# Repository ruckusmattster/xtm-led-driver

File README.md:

<div align="center">

# XTM LED Driver

**A flicker-free, four-decade DC LED driver for theatrical fixtures.**<br>
1.4 A down to 5 µA as pure DC: no PWM anywhere, nothing for a camera to catch.

[**Build guide**](docs/BUILD_GUIDE.md) ·
[**Design process**](docs/DESIGN_PROCESS.md) ·
[Hardware](docs/HARDWARE.md) ·
[Firmware](docs/FIRMWARE.md) ·
[Design record](docs/design-record/)

</div>

---

I'm building four stage fixtures around the **Xicato XTM19803050CCA** (19 mm LES, 3000 K, about
5000 lm at 1.4 A). Off-the-shelf drivers either dim with PWM, which rolling-shutter cameras turn
into bands, or bottom out around 1%, which makes the end of every fade snap to black. This
project is a two-board driver that does neither: the LED current is DC at every level from full
output down to 5 µA (0.0004%), fades are smooth enough to film in 240 fps slow motion, and each
fixture is a normal dimmable light in Home Assistant with a knob on the back and a sync button
that makes the others follow it.

Everything is here: the schematics (as code), the design calculations and simulations, scripted
KiCad 9 layouts that come out DRC-clean, Gerbers and placement files, BOMs with verified part
numbers, firmware for both boards with its tests, and the procedures to bring it up, calibrate
it and prove it doesn't flicker.

## Highlights

- **Four DC ranges, not PWM.** Four linear current sinks with 0.1 Ω, 1 Ω, 10 Ω and 100 Ω shunts
  sit in parallel under the LED. Each covers a decade at the same 14–140 mV sense voltage, so
  every range is equally precise, and a calibrated tail carries the last decade and a half to 5 µA.
- **Crossovers you can't see.** Where two ranges meet, both channels share the current on a
  log-domain blend, and the incoming channel idles at a small keep-alive current so it's already
  regulating when it's needed. Simulated deviation at a crossover: 0.14% on a 10 s fade.
- **A tracking buck that stays out of the picture.** A forced-PWM buck at 400 kHz holds the LED
  anode about 1 V above what the sinks need, set ahead of every current change by the MCU. Its
  ripple sits far above anything a camera or eye integrates.
- **Precision where it counts.** 16-bit DAC, zero-drift op-amps, Kelvin-sensed shunts (a
  four-terminal 0.1 Ω and 0.1% thin film for the rest), a guarded "precision island" on a 4-layer board. After calibration each range
  holds about ±0.1% of reading.
- **Real-time control on the driver.** An STM32G431 runs fades at 4 kHz, the crossovers, the
  headroom loop and the protection (a shorted LED clamps every sink within 100 µs). Wi-Fi never
  touches the light.
- **A friendly controller.** Board B is a socketed Waveshare ESP32-S3-Zero running ESPHome:
  Home Assistant light, rotary encoder with push, status LED, and fixture-to-fixture sync over
  ESP-NOW with authenticated packets. Every fixture also works completely on its own.
- **Layout by script.** Python scripts place every part, draw the critical copper by hand-coded
  rules, route the rest with Freerouting, pour and stitch ground, run DRC and export JLCPCB files.
  Both boards come out with 0 errors and 0 unconnected items.

## How it works

```mermaid
flowchart TB
  mains(["Mains"]) --> psu["Mean Well LRS-100-48<br/>isolated 48 V, off-board"]
  subgraph A["Board A · driver · 90 × 60 mm, 4 layers"]
    fuse["Fuse + TVS"] --> buck["Tracking buck<br/>LMR38020, forced PWM"]
    fuse --> aux["Aux buck + LDOs<br/>5.5 V · 5 V · 3.3 V"]
    mcu["STM32G431<br/>4 kHz control loop"] -->|SPI| dac["DAC80504<br/>4 × 16-bit"]
    dac --> sinks["OPA4388 + 4 linear sinks<br/>0.1 Ω · 1 Ω · 10 Ω · 100 Ω"]
    mcu -->|"DAC → feedback"| buck
    sinks -.->|"cathode tap<br/>fast trip"| mcu
  end
  subgraph L["LED"]
    led(["Xicato XTM<br/>up to 1.4 A"])
  end
  subgraph B["Board B · controller · 60 × 45 mm"]
    knob["Encoder · push · sync"] --> esp["ESP32-S3-Zero<br/>ESPHome"]
  end
  ha(["Home Assistant"])
  other(["Other fixtures"])
  psu -->|"48 V DC"| fuse
  buck -->|"LED+"| led
  led -->|"LED−"| sinks
  mcu ---|"10-way ribbon<br/>UART · 5.5 V · reset"| esp
  esp -.-|"Wi-Fi"| ha
  esp -.-|"ESP-NOW"| other
```

The **sinks** set the LED current; the **buck** only supplies the voltage they need. Board A's
MCU knows the LED's forward voltage at every current (it learns it as it runs), so on a rising
cue it raises the buck first and then the current, and on a falling cue the reverse. Only a
level, a fade time and status cross the ribbon to Board B.

<picture>
  <source media="(prefers-color-scheme: dark)" srcset="docs/images/ranges-dark.png">
  
</picture>

Brightness is exponential in the setting, so every step looks the same size: 1% of the scale is
about 13% more light, from 5 µA at the bottom to 1.4 A at the top.

<picture>
  <source media="(prefers-color-scheme: dark)" srcset="docs/images/curve-dark.png">
  
</picture>

## The boards

| | Board A: driver | Board B: controller |
| --- | --- | --- |
| **Top** |  |  |
| **Bottom** |  |  |
| Size | 90 × 60 mm, 4 layers, ENIG | 60 × 45 mm, 2 layers, ENIG |
| Parts | 206 on 96 nets | 42 on 32 nets |
| Does | 48 V in, tracking buck, four sinks, protection, fades, calibration | Wi-Fi and Home Assistant, knob, sync, status LED |
| Key parts | STM32G431CBU6, DAC80504, OPA4388, 2 × LMR38020, NDT3055L, WSK2512 | Waveshare ESP32-S3-Zero-M on sockets, Bourns PEC11R encoder |
| Layout result | 0 DRC errors, 0 unconnected | 0 DRC errors, 0 unconnected |

Renders are bare boards from KiCad (no 3D models for the parts). The ESP32-S3-Zero plugs into
two sockets on Board B's back, so it can be pulled out and flashed over its own USB-C.

## Specifications

Design values from the calculations and simulations in [`design/`](design/). None of this has
been measured on hardware yet.

| Parameter | Design value |
| --- | --- |
| Output | 5 µA to 1.4 A DC (1.5 A with tolerance), four ranges plus a calibrated tail |
| Brightness curve | Exponential: 0–100% → 5 µA–1.4 A, about 13% more light per 1% step |
| Flicker target | Under 1% at any frequency from 100 Hz to 20 kHz, at every level and during fades |
| Accuracy after calibration | ±0.09–0.11% RSS in each range; ±0.6% at 14 µA and ±1.6% at 5 µA |
| Crossover smoothness | 0.11–0.14% on a 10 s full-range fade, 0.9–1.5% on a 1 s fade (simulated) |
| Response | Snaps within 5 ms; fades updated at 4 kHz, from instant to 10 minutes |
| Input | 48 V DC (43.2–52.8 V) from a Mean Well LRS-100-48; about 45 W at full output |
| LED voltage | 3.5 V floor to 38 V usable, 40.4 V hard ceiling |
| Protection | Shorted LED (every sink clamped within 50–100 µs), open LED, undervoltage, four temperature sensors with derating, DAC read-back, watchdog, 3 A fuse, TVS on input and output |
| Link loss | Board A blinks twice and settles at 20% if Board B goes quiet; planned restarts hold the level |
| Control | Home Assistant (ESPHome native API), encoder with push, sync button and a header for a panel-mount button |
| Group sync | ESP-NOW broadcast, fixture to fixture, HMAC-SHA256 authenticated; no router or HA in the path |

## Status

| Stage | State |
| --- | --- |
| ✅ Circuit design, calculations, crossover simulation | Done; `design/calc.py` asserts the limits that matter |
| ✅ Schematics (as code) with connectivity check | Done; 0 ERC errors on both boards |
| ✅ Part numbers | Every numbered part checked against a distributor or manufacturer page (29 Sep 2026) |
| ✅ PCB layout | Done by script; both boards 0 DRC errors, 0 unconnected |
| ✅ Board A firmware | Builds (50–58 KB of 126 KB, depending on the toolchain); 97,146 host-test checks pass |
| ✅ Board B firmware | ESPHome config validates; 89 unit checks and a 43-check end-to-end test on ESPHome's Linux build pass |
| ⏳ ESP32-S3 build | Not yet run; the CI workflow in `.github/workflows/` runs it on every push |
| ⏳ Fabrication, assembly, bring-up, flicker measurements | Not started |
| ⚠️ Known firmware issue | Board A detects an open LED only near full output, and learns a bad correction while the LED is disconnected; see [known issues](docs/FIRMWARE.md#known-issues) |

If you build one before I do, I'd love to hear how it went.

## Repository map

```text
xtm-led-driver/
├── design/                 schematics as code, calculations, simulation
│   ├── board_a.py          every Board A part and pin-to-net connection
│   ├── board_b.py          the same for Board B
│   ├── catalog.py          part data: MPNs, LCSC numbers, footprints, verification notes
│   ├── build.py            regenerates hardware/ and runs the connectivity check (ERC)
│   ├── calc.py             every design number; prints calc_output.txt
│   ├── sim/handover.c      time-domain model of a crossover between two sinks
│   ├── compare_netlists.py checks your own KiCad schematic against the generated netlist
│   └── kicad_pos_to_jlc_cpl.py   KiCad position file → JLCPCB CPL, with rotation fixes
├── hardware/               generated from design/: per board, sheet tables, netlist, BOMs
│   ├── board_a/  board_b/
│   ├── board_a.kicad_dru   custom DRC rules (48 V spacing, precision-island clearance)
│   └── LAYOUT.md           the layout rules the scripts follow and you review against
├── layout/                 scripted KiCad 9 layout + Freerouting
│   ├── run_layout.bat      Windows launcher (double-click)
│   ├── make_board.py       stages: place, route, pour, stitch, DRC, export
│   ├── board_a_layout.py   Board A placement, hand-drawn copper, pours, rules
│   ├── board_b_layout.py   Board B the same
│   ├── lib/XTM.pretty/     this project's ESP32-S3-Zero socket footprint
│   └── out/                the finished boards: KiCad projects, Gerbers, CPL, DRC reports
├── firmware/
│   ├── board-a/            STM32G431 firmware in C (CMake), host tests, calibrate.py, flicker.py
│   └── board-b/            ESPHome configs + the xtm_driver external component, tests
└── docs/
    ├── BUILD_GUIDE.md      how to use these files and build the whole thing
    ├── DESIGN_PROCESS.md   how the design got here, and why
    ├── HARDWARE.md         circuit reference
    ├── FIRMWARE.md         firmware reference
    └── design-record/      the Phase 1 review and Phase 2 detailed design, as written
```

## Quick start

**Just want the boards?** The finished layouts are in [`layout/out/`](layout/out/): upload
`board_a-gerbers.zip` and `board_b-gerbers.zip` to JLCPCB with the settings in
[the build guide](docs/BUILD_GUIDE.md#6-order-the-pcbs-and-stencils), and order parts from the
hand-assembly BOMs in [`hardware/`](hardware/). Read [section 5](docs/BUILD_GUIDE.md#5-review-before-ordering)
first.

**Want to check or change the design?**

```sh
python3 design/build.py            # regenerate netlists and BOMs, run the connectivity check
python3 design/calc.py             # every design number (needs numpy, and gcc for the simulation)
make -C firmware/board-a/tests     # Board A host tests
make -C firmware/board-b/tests     # Board B unit tests
layout\run_layout.bat              # both layouts, on Windows with KiCad 9 and Java 21
```

**Building the firmware?**

```sh
cd firmware/board-a
cmake -B build -G Ninja -DCMAKE_TOOLCHAIN_FILE=cmake/arm-none-eabi.cmake && cmake --build build

cd ../board-b
cp secrets.yaml.example secrets.yaml   # fill in Wi-Fi and keys
esphome run xtm-1.yaml
```

The [build guide](docs/BUILD_GUIDE.md) walks through all of it, from installing the tools to a
calibrated, flicker-tested fixture.

## Documentation

| Document | What's in it |
| --- | --- |
| [Build guide](docs/BUILD_GUIDE.md) | Every step to make one yourself: tools, files, ordering, assembly, flashing, bring-up, calibration, flicker testing, use, troubleshooting, pinouts |
| [Design process](docs/DESIGN_PROCESS.md) | From a 0–10 V dimmer idea to this: the requirements, the reviews, the decisions and what changed them |
| [Hardware reference](docs/HARDWARE.md) | Both boards block by block, with values and the reasoning behind them |
| [Firmware reference](docs/FIRMWARE.md) | Board A's control loop, the link protocol, the ESPHome component |
| [Layout scripts](layout/README.md) | Running and changing the automated layout |
| [Layout rules](hardware/LAYOUT.md) | Stackup, floorplan, power and sense routing, clearances |
| [Design record](docs/design-record/) | The Phase 1 review and the Phase 2 detailed design, complete, as written |

## The design in one chart

The first plan used PWM for the bottom decade and handed the current between ranges with a
simple crossfade. Working through the dynamics showed the crossfade would dip the light by up to
17% on a fast fade, because the incoming channel starts from a wound-down integrator. Priming it
with a keep-alive current and blending in the log domain fixed it:

<picture>
  <source media="(prefers-color-scheme: dark)" srcset="docs/images/crossover-dark.png">
  
</picture>

That story, and the others like it, are in [the design process](docs/DESIGN_PROCESS.md).

## Safety

Board A runs from 48 V and can put 38 V on the LED connector. Neither board carries mains: the
48 V comes from a separate, certified, isolated supply (Mean Well LRS-100-48) with its own fused
inlet. Wire and enclose the mains side of that supply properly, or have someone qualified do it.
Never plug or unplug the LED while the output is on.

## Acknowledgements

- [KiCad](https://www.kicad.org), [Freerouting](https://github.com/freerouting/freerouting),
  [ESPHome](https://esphome.io) and [Home Assistant](https://www.home-assistant.io) do the heavy
  lifting.
- `firmware/board-a/third_party/` carries Arm's CMSIS (Apache-2.0) and ST's STM32G4 device files
  (Apache-2.0) and LL drivers (BSD-3-Clause), under their own licences.
- The ESP32-S3-Zero footprint's pin order was cross-checked against
  [jtomka/kicad-esp32-s3-zero](https://github.com/jtomka/kicad-esp32-s3-zero).

## License

Not chosen yet. Until a `LICENSE` file is added, the default applies: all rights reserved,
except the third-party files under their own licences.

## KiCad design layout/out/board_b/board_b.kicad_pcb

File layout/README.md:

# Board layout scripts

These scripts turn the two netlists in `design/` into finished KiCad 9 boards and JLCPCB files,
without anyone drawing the layout by hand. For each board they:

1. build the outline, mounting holes, slots and keep-outs, and place every part: the connectors,
   ICs and power parts at fixed coordinates, the small parts next to the pins they serve;
2. draw the copper that decides whether the board works before anything is routed: both switch
   nodes and bootstrap links (L1 only, no vias), the fused 48 V input and the +48V trunk to the
   buck, Q1's source to its shunt, the ch2 shunt ladder's bus bars, the CATHODE tab copper and heat
   spreader with its vias, the L2 ground plane, escapes for the few pins the router can't get out
   of, and a via to the plane beside every ground pad, while there's still room for them;
3. route everything else with Freerouting (kept out of the CATHODE copper), clean up what it
   leaves (stubs, doubled segments, dangling vias), and route again whatever is still open;
4. pour ground, stitch every pour fragment and pad the pours miss, place the reference labels;
5. run KiCad's DRC with the project's custom rules (`hardware/board_x.kicad_dru`: the 48 V
   spacing from IPC-2221B, 0.5 mm where a bare pad is involved and 0.3 mm between coated tracks;
   2 mm between precision and HV nets; 10 mm from the switch nodes; no vias on them);
6. export Gerbers, drill files and a JLCPCB placement file, and preview images.

The result is a normal KiCad project you open, inspect and adjust like one you drew yourself.

## What you need

- **KiCad 9.0** (any 9.0.x) from https://www.kicad.org/download/windows/ , installed to its default
  folder. Nothing else from KiCad: the scripts use its own Python and `kicad-cli`.
- **A Java 21 runtime** for Freerouting. From a Command Prompt:
  `winget install EclipseAdoptium.Temurin.21.JRE` (or the Temurin 21 JRE installer from
  https://adoptium.net with "Add to PATH" ticked). Open a new Command Prompt afterwards.
- **Internet on the first run**, to download Freerouting 1.9.0 (5 MB, from its GitHub releases)
  into `layout\tools\`. If that's blocked, download `freerouting-1.9.0.jar` from
  https://github.com/freerouting/freerouting/releases/tag/v1.9.0 into `layout\tools\` yourself, or
  set `FREEROUTING_JAR` to where you put it. (Board B's footprint for the ESP32-S3-Zero on its
  sockets is this project's own, in `lib\XTM.pretty`.)

Freerouting 1.9.0 rather than the newer 2.x on purpose: on Board A, 2.1 left over a hundred
connections open where 1.9 leaves a handful, and 2.1 ignores its pass limit.

## Running it

Double-click `run_layout.bat`, or from a Command Prompt in this folder:

```bat
run_layout.bat                          :: both boards, start to finish
run_layout.bat board_b                  :: one board
run_layout.bat board_a --stage place    :: placement only, with a preview (a minute)
run_layout.bat board_a --attempts 10    :: more routing attempts (each board tries 6 by default)
```

Board B takes a few minutes and Board A 5 to 30, most of it in Freerouting, which opens its own
window while it works and closes it when it's done: leave it alone. The same command in the
"KiCad 9.0 Command Prompt" (Start menu) is `python make_board.py board_a`.

Each run writes `out\board_a\` (or `board_b`):

| File | What it is |
| --- | --- |
| `board_a.kicad_pro`, `.kicad_pcb`, `.kicad_dru` | The KiCad project: open the `.kicad_pro` |
| `board_a-gerbers.zip` | Gerbers and drill files for JLCPCB, ready to upload |
| `board_a-cpl-jlc.csv` | Placement file in JLCPCB's format (`board_a-pos.csv` is KiCad's own) |
| `board_a_drc.json` | The final DRC report |
| `board_a-1-FCu_FSilkS.png` and the others | Preview images of each copper layer (SVG if no PNG converter) |
| `board_a_run.log` | What happened, with the DRC summary at the end |
| `board_a_freerouting-1.log`, `.dsn`, `.ses` | The router's input, output and log |

The last line of the log reads `done in ... s: 0 DRC errors, 0 unconnected` when the board is
complete. `run_layout.bat` says so too, and exits with an error otherwise.

## If connections are left open

Freerouting's result changes from run to run. If the log ends with a few connections open:

1. Run the board again, perhaps with `--attempts 10`; each attempt clears a wider circle
   around what's still open before routing it again; or
2. open `out\board_a\board_a.kicad_pro` in KiCad, route the ratsnest lines that remain (they're
   listed in the log), press **B** to refill the zones, save, close KiCad, and run
   `run_layout.bat board_a --stage export`. That re-stitches the pours, re-runs the DRC and writes
   new Gerbers and placement files without touching anything you drew.

The export stage is also how to regenerate the outputs after any hand edit. Running the full
script again starts over from the netlist and discards hand edits.

## Checking the result before ordering

Open each `.kicad_pro` in KiCad 9 and go through this list. The DRC covers the numeric rules; these
are the things a rule can't see.

- **Inspect > Design Rules Checker**, "Refill all zones" ticked: no errors, nothing unconnected.
  Silkscreen warnings are fine; look at any that sit on a pad.
- **View > 3D Viewer**: every part present and on the right side; J1, J2 and J3's openings face
  off the board. Board B's U1 is on the back, shown by its outline on the F.Fab/B.Fab layers
  (there's no 3D model for the module).
- Board A power stage: U2's SW pin, C23 and L2 pad 1 joined by short, wide copper on L1 with no
  vias (the same for U3, C3 and L3); C22 right at U2's VIN pin with a ground via beside it.
- Board A cathode: J2 pin 1, C60, R110 and the four drains all on the tab copper; the heat
  spreader under it on the bottom layer, joined by the grid of vias; R102 at least 2 mm from it.
- Board A sinks: each channel's SNSHI and SNSLO tracks start at the shunt's Kelvin pads (R102
  pads 2 and 3; NT1/NT2 at the ladder's mid-points; NT3–NT6 at R100 and R101); the divider
  bottoms (R46, R48, R50, R52) and C44–C47 return to SNSLO, not to ground.
- Board A precision island: nothing from the switch nodes nearby; the DRC's 2 mm rule keeps HV
  copper away.
- Board B: U1's two socket rows on the back, pin 1 (square pad) at the USB-C end nearest the
  middle of the board; no copper on either side under the antenna end at the right-hand edge.
  Print the board 1:1 (File > Plot, B.Cu, B.SilkS and Edge.Cuts to PDF, mirrored) and lay the
  module on it, pins into the pads, before ordering.
- Holes: Board A's four M3 holes and Board B's two are unplated, with nothing inside their rings.
- The Gerbers in KiCad's Gerber viewer (or JLCPCB's): four copper layers for Board A and two for
  Board B, the slot between J2's pads in the drill/outline file, paste layers present.

References that didn't fit on the silkscreen are on the F.Fab layer: for hand assembly, print it
(File > Plot, F.Fab and Edge.Cuts to PDF) as the assembly drawing.

At JLCPCB: upload the Gerber zip; for assembly, use `hardware/board_x/board_x-bom-jlc.csv` as the
BOM and `board_x-cpl-jlc.csv` as the placement file, and check every part's rotation in their
preview (their library's zero angle doesn't always match KiCad's; polarised parts and the ICs are
the ones to look at).

## What the scripts don't do

- They don't keep each Kelvin pair (SNSHIx with SNSLOx) side by side: the router draws them
  separately. They start at the right sense points, which is what matters most at these slow
  signals; redrawing them as pairs by hand is the one refinement worth the time.
- The router doesn't know which tracks matter more than others: look over the power stage, the
  sinks and the precision island against `hardware/LAYOUT.md` before ordering.
- Freerouting's result varies from run to run, and the placement of small parts follows simple
  rules; a second run can come out better or worse.

## Changing the layout

Everything that decides the layout is in `board_a_layout.py` and `board_b_layout.py`:

- `L.place("U2", 53.1, 40.5, 270)`: fixed parts, in mm from the board's top-left corner, rotation
  in degrees counter-clockwise. Move one, run `--stage place` to see it, then run the whole board.
- `A([...], Rect(x0, y0, x1, y1), anchor_pad=...)`: small parts placed automatically inside the
  rectangle, as close as possible to the pad named (decoupling capacitors) or to the parts they
  connect to. `SPACING` sets the room left between them for routing.
- `NET_CLASSES` and `PATTERNS`: track widths and clearances per net. The widths have to fit the
  pins a net lands on (0.2 mm reaches the 0.5 mm-pitch QFN pins).
- `prerouted()`, `cathode_copper()` and `finish()`: the copper drawn by hand and the pours.
- `SPEC`: how the board is routed: attempts and the time each may take, whether to start over
  every few attempts (`restart_every`, Board B) or keep repairing (Board A), the ground fan-out,
  and which nets are poured rather than routed.

The netlists themselves come from `design/board_a.py` and `design/board_b.py`; after changing
those, run `python design/build.py` (BOMs, sheet tables and netlists) and then the layout.

## Files

| File | Role |
| --- | --- |
| `make_board.py` | The run itself: stages, routing attempts, checks, outputs |
| `board_a_layout.py`, `board_b_layout.py` | Each board's placement, pre-drawn copper, pours and rules |
| `pcbkit.py` | Building a board from a netlist: footprints, placement, tracks, vias, zones, keep-outs |
| `route.py` | Freerouting round trip, clean-up, stitching, DRC, previews, fabrication outputs |
| `kicadlib.py` | Finds KiCad 9's footprint libraries, and this project's own in `lib\` |
| `run_layout.bat` | Windows launcher: finds KiCad and Java, runs both boards |

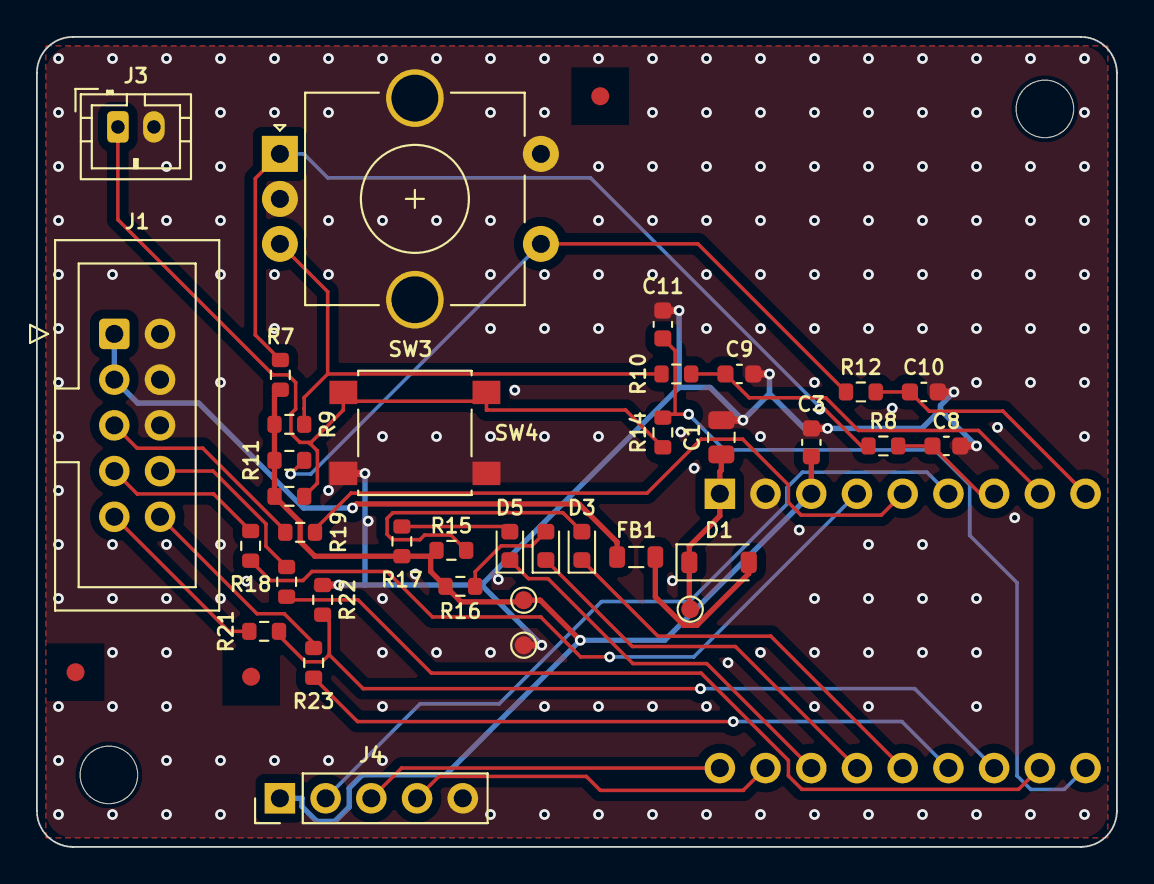
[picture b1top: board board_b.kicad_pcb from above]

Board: 2 copper layers, 60.0 x 45.0 mm, 42 parts (1 on the bottom side), 32 nets.

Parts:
C1: 10uF; C_0805_2012Metric
C3: 100nF; C_0603_1608Metric
C8, C9, C10, C11: 10nF; C_0603_1608Metric
D1: B5819W; D_SOD-123
D3: red; LED_0603_1608Metric
D4: green; LED_0603_1608Metric
D5: blue; LED_0603_1608Metric
FB1: 600R@100MHz 2A; L_0805_2012Metric
FID1, FID2, FID3: FID; Fiducial_1mm_Mask2mm
H1, H2: M3; MountingHole_3.2mm_M3
J1: 2x5 box header; IDC-Header_2x05_P2.54mm_Vertical
J3: JST PH 2; JST_PH_B2B-PH-K_1x02_P2.00mm_Vertical
J4: 1x5 header; PinHeader_1x05_P2.54mm_Vertical
R7, R8, R9, R10, R11, R12, R13, R14: 10k; R_0603_1608Metric
R15: 1k; R_0603_1608Metric
R16, R17: 220R; R_0603_1608Metric
R18, R19, R20, R21, R23: 100R; R_0603_1608Metric
R22: 100k; R_0603_1608Metric
SW3: PEC11R-4220F-S0024; RotaryEncoder_Alps_EC11E-Switch_Vertical_H20mm_CircularMoun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
SW4: SYNC; SW_SPST_B3S-1000
TP1, TP2, TP3: TP; TestPoint_Pad_D1.0mm
U1: ESP32-S3-Zero-M; ESP32-S3-Zero_Socket

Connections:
+3V3: C3.1, J4.1, R7.1, R9.1, R11.1, R13.1, R15.1, R16.1, R17.1, TP2.1, U1.3
+5V5_F: D1.2, FB1.2
+5V5_IN: FB1.1, J1.1, J1.3
+5V_SYS: C1.1, D1.1, TP1.1, U1.1
A_OK: J1.9, R21.1
A_OK_IN: R21.2, R22.1, U1.12
BOOT0_A: J1.8, R20.2
BOOT0_OUT: R20.1, U1.11
ENC_A: C8.1, R8.2, U1.7
ENC_A_RAW: R7.2, R8.1, SW3.A
ENC_B: C9.1, R10.2, U1.8
ENC_B_RAW: R9.2, R10.1, SW3.B
ENC_SW: C10.1, R12.2, U1.9
ENC_SW_RAW: R11.2, R12.1, SW3.S1
GND: C1.2, C3.2, C8.2, C9.2, C10.2, C11.2, J1.2, J1.4, J1.6, J3.2, J4.5, R22.2, SW3.C, SW3.MP, SW3.S2, SW4.2, TP3.1, U1.2
LED_B: D5.1, U1.16
LED_B_A: D5.2, R17.2
LED_G: D4.1, U1.15
LED_G_A: D4.2, R16.2
LED_R: D3.1, U1.14
LED_R_A: D3.2, R15.2
LINK_RX: R19.2, U1.5
LINK_TX: R18.1, U1.4
NRST_A: J1.10, R23.2
NRST_OUT: R23.1, U1.13
RXD_A: J1.7, R18.2
SPARE_IO3: J4.2, U1.6
SPARE_IO43: J4.3, U1.18
SPARE_IO44: J4.4, U1.17
SYNC: C11.1, R14.2, U1.10
SYNC_RAW: J3.1, R13.2, R14.1, SW4.1
TXD_A: J1.5, R19.1

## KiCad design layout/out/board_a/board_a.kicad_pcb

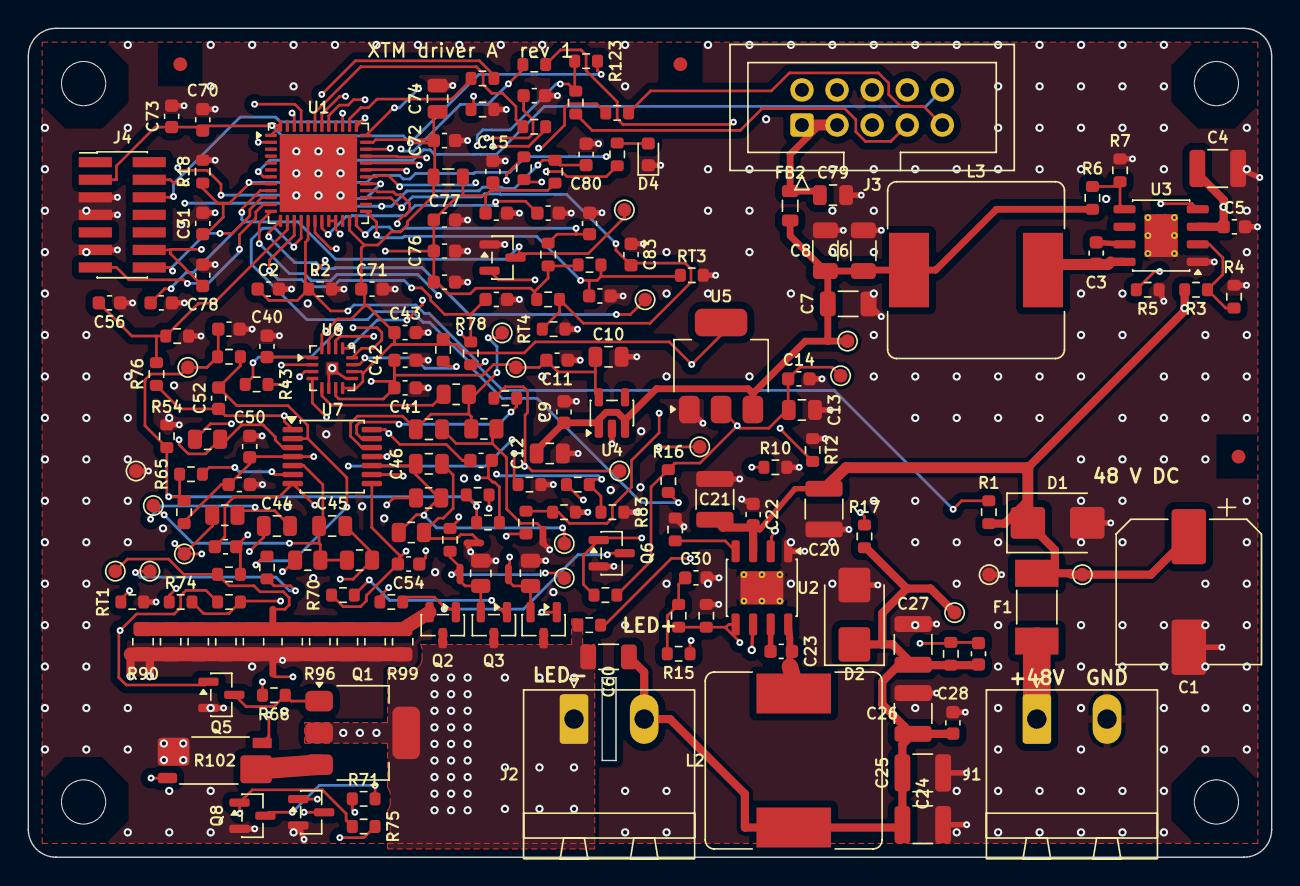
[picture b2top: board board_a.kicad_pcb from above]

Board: 4 copper layers, 90.0 x 60.0 mm, 206 parts (0 on the bottom side), 96 nets.

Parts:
C1: 47uF 100V; CP_Elec_10x10
C2, C31, C80, C81, C82, C83: 10nF; C_0603_1608Metric
C3, C11, C14, C16, C23, C41, C43, C50, C70, C71, C72, C73, C76, C77, C78: 100nF; C_0603_1608Metric
C4, C20, C21, C24, C25, C26, C27: 4.7uF 100V; C_1210_3225Metric
C5, C22, C28: 100nF 100V; C_0603_1608Metric
C6, C7, C8: 22uF; C_1206_3216Metric
C9, C15, C42, C48, C51, C75: 1uF; C_0603_1608Metric
C10, C12, C74: 4.7uF; C_0805_2012Metric
C13, C79: 10uF; C_0805_2012Metric
C29: 22pF C0G; C_0603_1608Metric
C30: 47nF; C_0603_1608Metric
C40: 220nF; C_0603_1608Metric
C44, C45, C46, C47: 10nF C0G; C_0805_2012Metric
C52, C53, C54, C55: 2.2nF C0G; C_0603_1608Metric
C56, C57, C58, C59, C61: 1nF C0G; C_0603_1608Metric
C60: 22nF 100V; C_1206_3216Metric
D1: SMBJ58A; D_SMB
D2: SMBJ43A; D_SMB
D3: BAV199; SOT-23
D4: green; LED_0603_1608Metric
F1: 3A T; Fuse_Littelfuse-NANO2-451_453
FB1: 600R@100MHz; L_0805_2012Metric
FB2: 600R@100MHz 2A; L_0805_2012Metric
FID1, FID2, FID3: FID; Fiducial_1mm_Mask2mm
H1, H2, H3, H4: M3; MountingHole_3.2mm_M3
J1, J2: MSTBA 2,5/2-G-5,08; PhoenixContact_MSTBA_2,5_2-G-5,08_1x02_P5.08mm_Horizontal
J3: 2x5 box header; IDC-Header_2x05_P2.54mm_Vertical
J4: STDC14; PinHeader_2x07_P1.27mm_Vertical_SMD
L2: 33uH; L_Bourns_SRR1260
L3: 15uH; L_Bourns_SRR1260
NT1, NT2, NT3, NT4, NT5, NT6: NetTie; NetTie-2_SMD_Pad0.5mm
Q1: NDT3055L; SOT-223-3_TabPin2
Q2, Q5, Q6, Q7, Q8: 2N7002BK; SOT-23
Q3, Q4: 2N7002; SOT-23
R1, R6, R10, R16, R72, R73, R74, R75, R76, R77, R78, R79, R80, R81, R82, R83, R123: 100k; R_0603_1608Metric
R2: 6.2k; R_0603_1608Metric
R3: 280k; R_0603_1608Metric
R4, R44, R53, R120, R126, R127, R128, R129: 10k; R_0603_1608Metric
R5: 52.3k; R_0603_1608Metric
R7: 22.1k; R_0603_1608Metric
R11: 64.9k; R_0603_1608Metric
R12: 200k; R_0603_1608Metric
R13: 7.32k; R_0603_1608Metric
R14, R15: 8.25k; R_0603_1608Metric
R17, R110: 1M; R_0603_1608Metric
R18: 82k; R_0603_1608Metric
R40, R41, R42, R43: 22R; R_0603_1608Metric
R45, R47, R49, R51: 12.0k 0.1%; R_0805_2012Metric
R46, R48, R50, R52: 1.00k 0.1%; R_0805_2012Metric
R54, R60, R61, R62, R63, R125: 1k; R_0603_1608Metric
R64, R65, R66, R67: 1.82M; R_0603_1608Metric
R68, R69, R70, R71: 220R; R_0603_1608Metric
R90, R91, R92, R93, R94, R95, R96, R97, R98, R99, R100: 10R 0.1%; R_0805_2012Metric
R101: 100R 0.1%; R_0805_2012Metric
R102: 0.1R 4T; R_Shunt_Vishay_WSK2512_6332Metric_T1.19mm
R121, R122, R124: 100R; R_0603_1608Metric
RT1, RT2, RT3, RT4: 10k NTC; R_0603_1608Metric
TP1, TP2, TP3, TP4, TP5, TP6, TP7, TP8, TP9, TP10, TP11, TP12, TP13, TP14, TP15, TP16, TP17, TP18, TP19: TP; TestPoint_Pad_D1.0mm
U1: STM32G431CBU6; QFN-48-1EP_7x7mm_P0.5mm_EP5.6x5.6mm
U2, U3: LMR38020FDDAR; HSOP-8-1EP_3.9x4.9mm_P1.27mm_EP2.41x3.1mm_ThermalVias
U4: TPS7A2050PDBVR; SOT-23-5
U5: LDL1117S33R; SOT-223-3_TabPin2
U6: DAC80504RTET; Texas_RTE0016D_WQFN-16-1EP_3x3mm_P0.5mm_EP0.8x0.8mm
U7: OPA4388IPWR; TSSOP-14_4.4x5mm_P0.65mm

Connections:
+3V3: C13.1, C14.1, C43.1, C70.1, C71.1, C72.1, C73.1, C74.1, D3.2, FB1.1, J4.3, R16.2, R44.2, R72.2, R73.2, R74.2, R75.2, R123.2, TP4.1, U1.1, U1.23, U1.35, U1.48, U5.2, U6.8, U6.10, U6.16
+3V3A: C15.1, C16.1, C75.1, C76.1, C77.1, FB1.2, R126.1, R127.1, R128.1, R129.1, U1.20, U1.21
+5V5: C6.1, C7.1, C8.1, C9.1, C12.1, FB2.1, L3.2, R6.1, TP2.1, U4.1, U4.3, U5.3
+5V5_LINK: C79.1, FB2.2, J3.1, J3.3
+5VA: C10.1, C11.1, C41.1, C42.1, C50.1, C51.1, R53.1, TP3.1, U4.5, U6.7, U7.4
+48V: C1.1, C4.1, C5.1, C20.1, C21.1, C22.1, D1.1, F1.2, R1.1, R3.1, TP1.1, U2.3, U3.3
+48V_RAW: F1.1, J1.1
AUX_BOOT: C3.1, U3.7
AUX_EN: R3.2, R4.1, U3.2
AUX_FB: R6.2, R7.1, U3.5
AUX_RT: R5.1, U3.4
AUX_SW: C3.2, L3.1, U3.8
A_OK: J3.9, R124.2
A_OK_MCU: R124.1, U1.33
BIAS: C48.1, R53.2, R54.1, R64.1, R65.1, R66.1, R67.1, TP7.1
BOOT0: J3.8, R120.1, U1.46
BUCK_BOOT: C23.1, U2.7
BUCK_DAC: R15.2, TP10.1, U1.12
BUCK_EN: R10.1, U1.2, U2.2
BUCK_FB: C29.2, R12.2, R13.1, R14.1, U2.5
BUCK_PG: R16.1, U1.16, U2.6
BUCK_RT: R11.1, U2.4
BUCK_SW: C23.2, L2.1, U2.8
CATHODE: C60.2, J2.1, Q1.2, Q2.3, Q3.3, Q4.3, R110.1
CATH_TAP: C61.1, D3.3, R110.2, TP6.1, U1.9
CLAMP1: Q5.1, R72.1, U1.29
CLAMP2: Q6.1, R73.1, U1.30
CLAMP3: Q7.1, R74.1, U1.39
CLAMP4: Q8.1, R75.1, U1.45
DAC_CS: R40.2, U6.12
DAC_LDAC: R44.1, U6.11
DAC_OUT1: R45.1, U6.2
DAC_OUT2: R47.1, U6.3
DAC_OUT3: R49.1, U6.4
DAC_OUT4: R51.1, U6.5
DAC_REF: C40.1, U6.1
DAC_SCLK: R41.2, U6.13
DAC_SDI: R42.2, U6.14
DAC_SDO: R43.1, U6.15
GATE1: Q1.1, Q5.3, R68.2
GATE2: Q2.1, Q6.3, R69.2
GATE3: Q3.1, Q7.3, R70.2
GATE4: Q4.1, Q8.3, R71.2
GDRV1: C52.1, R68.1, R76.1, U7.1
GDRV2: C53.1, R69.1, R78.1, U7.7
GDRV3: C54.1, R70.1, R80.1, U7.8
GDRV4: C55.1, R71.1, R82.1, U7.14
GMON1: C56.1, R76.2, R77.1, U1.14
GMON2: C57.1, R78.2, R79.1, U1.15
GMON3: C58.1, R80.2, R81.1, U1.19
GMON4: C59.1, R82.2, R83.1, U1.28
GND: C1.2, C2.2, C4.2, C5.2, C6.2, C7.2, C8.2, C9.2, C10.2, C11.2, C12.2, C13.2, C14.2, C15.2, C16.2, C20.2, C21.2, C22.2, C24.2, C25.2, C26.2, C27.2, C28.2, C30.2, C31.2, C40.2, C41.2, C42.2, C43.2, C48.2, C50.2, C51.2, C56.2, C57.2, C58.2, C59.2, C61.2, C70.2, C71.2, C72.2, C73.2, C74.2, C75.2, C76.2, C77.2, C78.2, C79.2, C80.2, C81.2, C82.2, C83.2, D1.2, D2.2, D3.1, D4.1, J1.2, J3.2, J3.4, J3.6, J4.5, J4.7, J4.11, NT2.1, NT4.1, NT6.1, Q5.2, Q6.2, Q7.2, Q8.2, R2.2, R4.2, R5.2, R7.2, R10.2, R11.2, R13.2, R18.2, R54.2, R77.2, R79.2, R81.2, R83.2, R90.2, R91.2, R92.2, R93.2, R94.2, R95.2, R96.2, R97.2, R98.2, R99.2, R100.2, R101.2, R102.4, R120.2, RT1.2, RT2.2, RT3.2, RT4.2, TP8.1, TP9.1, U1.49, U2.1, U2.9, U3.1, U3.9, U4.2, U5.1, U6.6, U6.9, U6.17, U7.11
INJ_MID: C30.1, R14.2, R15.1
LED_STAT: R125.1, U1.34
LED_STAT_A: D4.2, R125.2
LINK_RX: R122.2, R123.1, U1.32
LINK_TX: R121.1, U1.31
MCU_DAC_CS: R40.1, U1.38
MCU_MISO: R43.2, U1.42
MCU_MOSI: R42.1, U1.43
MCU_SCLK: R41.1, U1.41
NINV1: C52.2, R60.2, R64.2, U7.2
NINV2: C53.2, R61.2, R65.2, U7.6
NINV3: C54.2, R62.2, R66.2, U7.9
NINV4: C55.2, R63.2, R67.2, U7.13
NRST: C78.1, J3.10, J4.12, U1.7
NTC1: C80.1, R126.2, RT1.1, U1.18
NTC2: C81.1, R127.2, RT2.1, U1.24
NTC3: C82.1, R128.2, RT3.1, U1.25
NTC4: C83.1, R129.2, RT4.1, U1.27
RXD_A: J3.7, R122.1
SET1: C44.1, R45.2, R46.1, TP12.1, U7.3
SET2: C45.1, R47.2, R48.1, TP14.1, U7.5
SET3: C46.1, R49.2, R50.1, TP16.1, U7.10
SET4: C47.1, R51.2, R52.1, TP18.1, U7.12
SNSHI1: R60.1, R102.2, TP13.1
SNSHI2: NT1.2, R61.1, TP15.1
SNSHI3: NT3.2, R62.1, TP17.1
SNSHI4: NT5.2, R63.1, TP19.1
SNSLO1: C44.2, R46.2, R102.3
SNSLO2: C45.2, NT2.2, R48.2
SNSLO3: C46.2, NT4.2, R50.2
SNSLO4: C47.2, NT6.2, R52.2
SPARE_PA5: TP11.1, U1.13
SRC1: Q1.3, R102.1
SRC2: NT1.1, Q2.2, R90.1, R91.1, R92.1, R93.1, R94.1, R95.1, R96.1, R97.1, R98.1, R99.1
SRC3: NT3.1, Q3.2, R100.1
SRC4: NT5.1, Q4.2, R101.1
SWCLK: J4.6, U1.37
SWDIO: J4.4, U1.36
TXD_A: J3.5, R121.2
V48_SENSE: C2.1, R1.2, R2.1, U1.17
VCP_RX: J4.13, U1.11
VCP_TX: J4.14, U1.10
VOUT: C24.1, C25.1, C26.1, C27.1, C28.1, C29.1, C60.1, D2.1, J2.2, L2.2, R12.1, R17.1, TP5.1
VOUT_SENSE: C31.1, R17.2, R18.1, U1.8

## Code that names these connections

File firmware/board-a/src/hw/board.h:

/* Board A pin map (matches design/board_a.py, sheet A6). */
#ifndef BOARD_H
#define BOARD_H

#include "stm32g4xx.h"

/* gate clamps ch1..ch4: high = clamp on (gate held low). Pulled up in hardware. */
#define CLAMP1_PORT GPIOC
#define CLAMP1_PIN  LL_GPIO_PIN_6
#define CLAMP2_PORT GPIOA
#define CLAMP2_PIN  LL_GPIO_PIN_8
#define CLAMP3_PORT GPIOC
#define CLAMP3_PIN  LL_GPIO_PIN_10
#define CLAMP4_PORT GPIOB
#define CLAMP4_PIN  LL_GPIO_PIN_7

/* PC13, not PB9: the ROM bootloader drives PB9 (its FDCAN1_TX) high, and PC13 has no bootloader
 * function, so R10's 100k pull-down keeps the buck off in reset, in the bootloader and when unprogrammed. */
#define BUCK_EN_PORT GPIOC
#define BUCK_EN_PIN  LL_GPIO_PIN_13
#define BUCK_PG_PORT GPIOC
#define BUCK_PG_PIN  LL_GPIO_PIN_4

#define LED_PORT GPIOA
#define LED_PIN  LL_GPIO_PIN_12
#define AOK_PORT GPIOA
#define AOK_PIN  LL_GPIO_PIN_11

#define DAC_CS_PORT GPIOA
#define DAC_CS_PIN  LL_GPIO_PIN_15

/* analog inputs */
#define ADC1_CH_VOUT  LL_ADC_CHANNEL_1    /* PA0 */
#define ADC1_CH_CATH  LL_ADC_CHANNEL_2    /* PA1, also COMP1_INP */
#define ADC1_CH_V48   LL_ADC_CHANNEL_15   /* PB0 */
#define ADC1_CH_NTC1  LL_ADC_CHANNEL_12   /* PB1  FET */
#define ADC1_CH_NTC2  LL_ADC_CHANNEL_14   /* PB11 main buck */
#define ADC1_CH_NTC3  LL_ADC_CHANNEL_11   /* PB12 aux rails */
#define ADC1_CH_NTC4  LL_ADC_CHANNEL_5    /* PB14 precision section */
#define ADC2_CH_GMON1 LL_ADC_CHANNEL_3    /* PA6 */
#define ADC2_CH_GMON2 LL_ADC_CHANNEL_4    /* PA7 */
#define ADC2_CH_GMON3 LL_ADC_CHANNEL_12   /* PB2 */
#define ADC2_CH_GMON4 LL_ADC_CHANNEL_15   /* PB15 */

#endif

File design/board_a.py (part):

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    b.two("C50", "C_100N", "+5VA", "GND", s)
    b.two("C51", "C_1U", "+5VA", "GND", s)
    fets = {1: ("Q1", "NDT3055L"), 2: ("Q2", "2N7002BK"), 3: ("Q3", "2N7002"), 4: ("Q4", "2N7002")}
    clamp_pin = {1: "CLAMP1", 2: "CLAMP2", 3: "CLAMP3", 4: "CLAMP4"}
    for k in (1, 2, 3, 4):
        n = 60 + (k - 1)
        b.two(f"R{n}", "R_1K", f"SNSHI{k}", f"NINV{k}", s)                        # R60-R63  R_IN
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    s = "A5"
    b.two("J2", "MSTBA2", "CATHODE", "VOUT", s,
          note="Pin 1 LED- (toward the sinks), pin 2 LED+ (red lead, toward the buck); a 1 mm slot between the pads")
    b.two("C60", "C_22N_100V", "VOUT", "CATHODE", s, note="C_a: directly across J2's pins")
    b.two("R110", "R_1M", "CATHODE", "CATH_TAP", s)
    b.two("C61", "C_1N_C0G", "CATH_TAP", "GND", s)
    b.add("D3", "BAV199", {"1": "GND", "2": "+3V3", "3": "CATH_TAP"}, s)
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        "39": "CLAMP3", "40": NC, "41": "MCU_SCLK", "42": "MCU_MISO", "43": "MCU_MOSI", "44": NC, "45": "CLAMP4",
        "46": "BOOT0", "47": NC, "48": "+3V3", "49": "GND"}, s,
        note="Exposed pad is VSS: solder it and stitch it to GND. PB6 and PB4 carry the UCPD dead-battery pull-downs "
             "until firmware disables them, so no clamp sits on PB6. BUCK_EN is on PC13 because the ROM bootloader "
             "drives PB9 (its FDCAN1_TX) high; PC13 has no bootloader function, so R10 holds the buck off")
    for ref in ("C70", "C71", "C72", "C73"):
        b.two(ref, "C_100N", "+3V3", "GND", s)
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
